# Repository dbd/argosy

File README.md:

# Argosy

Maybe this will be a keyboard one day

### Credits
Footprints from: https://github.com/dnlbauer/corax-keyboard

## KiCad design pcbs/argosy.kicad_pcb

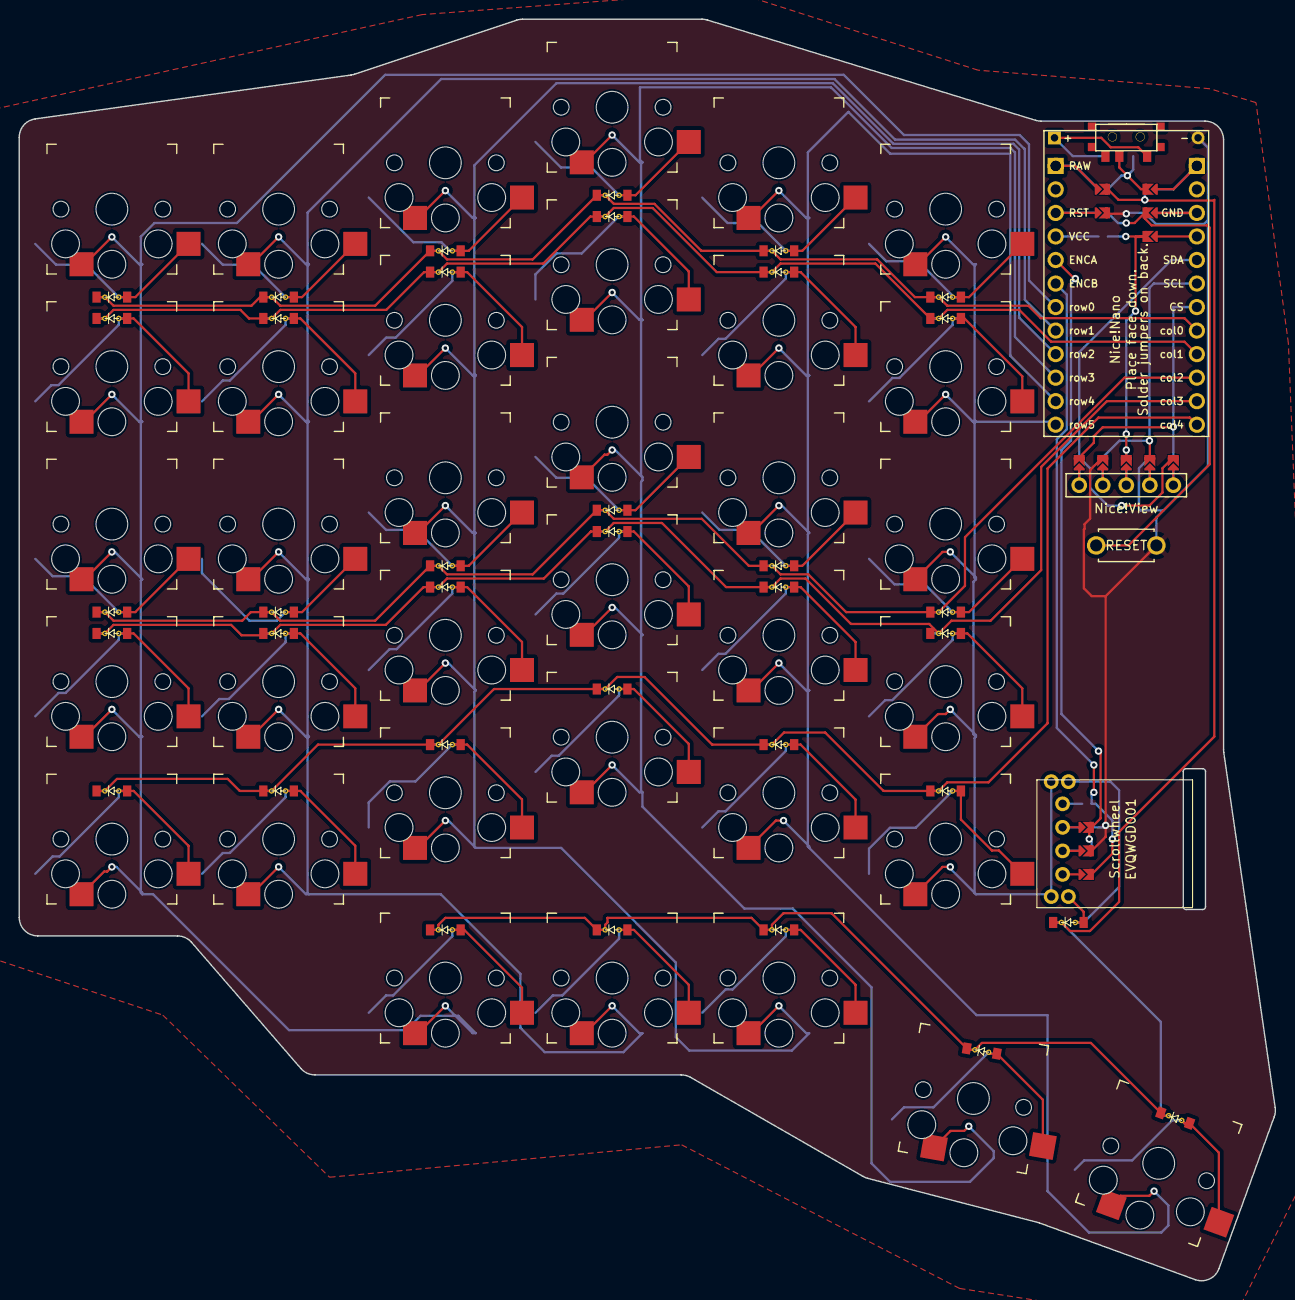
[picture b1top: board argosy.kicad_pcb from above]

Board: 2 copper layers, 135.6 x 136.2 mm, 103 parts (0 on the bottom side), 73 nets.

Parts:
Battery1: niceview_headers
D1, D2, D3, D4, D5, D6, D7, D8, D9, D10, D11, D12, D13, D14, D15, D16, D17, D18, D19, D20, D21, D22, D23, D24, D25, D26, D27, D28, D29, D30, D31, D32, D33, D34, D35, D36: ComboDiode
J1, J2, J3, J4, J5, J6, J7, J8, J9, J10, J11, J12, J13, J14, J15, J16, J17, J18, J19, J20, J21, J22, J23, J24, J25, J26: Jumper
MCU1: ProMicro
Nice!View1: niceview_headers
S1, S2, S3, S4, S5, S6, S7, S8, S9, S10, S11, S12, S13, S14, S15, S16, S17, S18, S19, S20, S21, S22, S23, S24, S25, S26, S27, S28, S29, S30, S31, S32, S33, S34, S35: PG1350
S36: RollerEncoder_Panasonic_EVQWGD001
T1: SPDT_C128955
_1: ResetSW

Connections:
CS: J21.2, J26.2, MCU1.19
ENCA: J3.2, J6.2, MCU1.5
ENCA_GND: J3.1, J5.1, S36.C
ENCB: J1.2, J4.2, MCU1.6
ENCB_undef: J1.1, S36.A
GND: Battery1.2, J2.2, J5.2, J10.2, J15.2, J20.2, J25.2, _1.2
GND_ENCA: J2.1, J6.1, S36.B
GND_RST: J10.1, J13.1, MCU1.15
GND_VCC: J14.1, MCU1.16
NN_CS_SDA: J21.1, J22.1, Nice!View1.1
NN_GND_SCL: J20.1, J23.1, Nice!View1.1
NN_SCL_GND: J18.1, J25.1, Nice!View1.3
NN_SDA_CS: J17.1, J26.1, Nice!View1.4
NN_VCC: J19.1, J24.1, Nice!View1.2
P1: D31.1, D32.1, D33.1, D34.1, D35.1, D36.1, J11.2, J16.2
P1_RAW: J11.1, J12.1, MCU1.13
RAW: J7.2, J12.2, T1.2
RAW_P1: J7.1, J16.1, MCU1.1
RST: J8.2, J13.2, _1.1
RST_GND: J8.1, J15.1, MCU1.3
SCL: J18.2, J23.2, MCU1.18
SDA: J17.2, J22.2, MCU1.17
VCC: J9.2, J14.2, J19.2, J24.2
VCC_GND: J9.1, MCU1.4
alt_cluster: D33.2, S33.2
col0: D2.1, D4.1, D6.1, D8.1, D10.1, D12.1, MCU1.20
col1: D15.1, D18.1, D21.1, D24.1, D27.1, D30.1, MCU1.21
col2: D1.1, D3.1, D5.1, D7.1, D9.1, D11.1, MCU1.22
col3: D14.1, D17.1, D20.1, D23.1, D26.1, D29.1, MCU1.23
col4: D13.1, D16.1, D19.1, D22.1, D25.1, D28.1, MCU1.24
end_cluster: D31.2, S31.2
index_home: D9.2, S23.2
index_lower: D26.2, S22.2
index_mods: D25.2, S21.2
index_number: D10.2, S25.2
index_upper: D27.2, S24.2
inner_home: D11.2, S28.2
inner_lower: D29.2, S27.2
inner_mods: D28.2, S26.2
inner_number: D12.2, S30.2
inner_upper: D30.2, S29.2
layer_cluster: D35.2, S35.2
middle_home: D7.2, S18.2
middle_lower: D23.2, S17.2
middle_mods: D22.2, S16.2
middle_number: D8.2, S20.2
middle_upper: D24.2, S19.2
mute_cluster: D32.2, S32.2
outer_home: D1.2, S3.2
outer_lower: D14.2, S2.2
outer_mods: D13.2, S1.2
outer_number: D2.2, S5.2
outer_upper: D15.2, S4.2
pinky_home: D3.2, S8.2
pinky_lower: D17.2, S7.2
pinky_mods: D16.2, S6.2
pinky_number: D4.2, S10.2
pinky_upper: D18.2, S9.2
ring_home: D5.2, S13.2
ring_lower: D20.2, S12.2
ring_mods: D19.2, S11.2
ring_number: D6.2, S15.2
ring_upper: D21.2, S14.2
row0: MCU1.7, S1.1, S2.1, S3.1, S4.1, S5.1, S31.1
row1: MCU1.8, S6.1, S7.1, S8.1, S9.1, S10.1, S32.1
row2: MCU1.9, S11.1, S12.1, S13.1, S14.1, S15.1, S33.1
row3: MCU1.10, S16.1, S17.1, S18.1, S19.1, S20.1, S34.1
row4: MCU1.11, S21.1, S22.1, S23.1, S24.1, S25.1, S35.1
row5: MCU1.12, S26.1, S27.1, S28.1, S29.1, S30.1, S36.S1
scrollwheel_scrollwheel: D36.2, S36.S2
space_cluster: D34.2, S34.2
switch_from: Battery1.1, T1.1
undef_ENCB: J4.1, S36.D

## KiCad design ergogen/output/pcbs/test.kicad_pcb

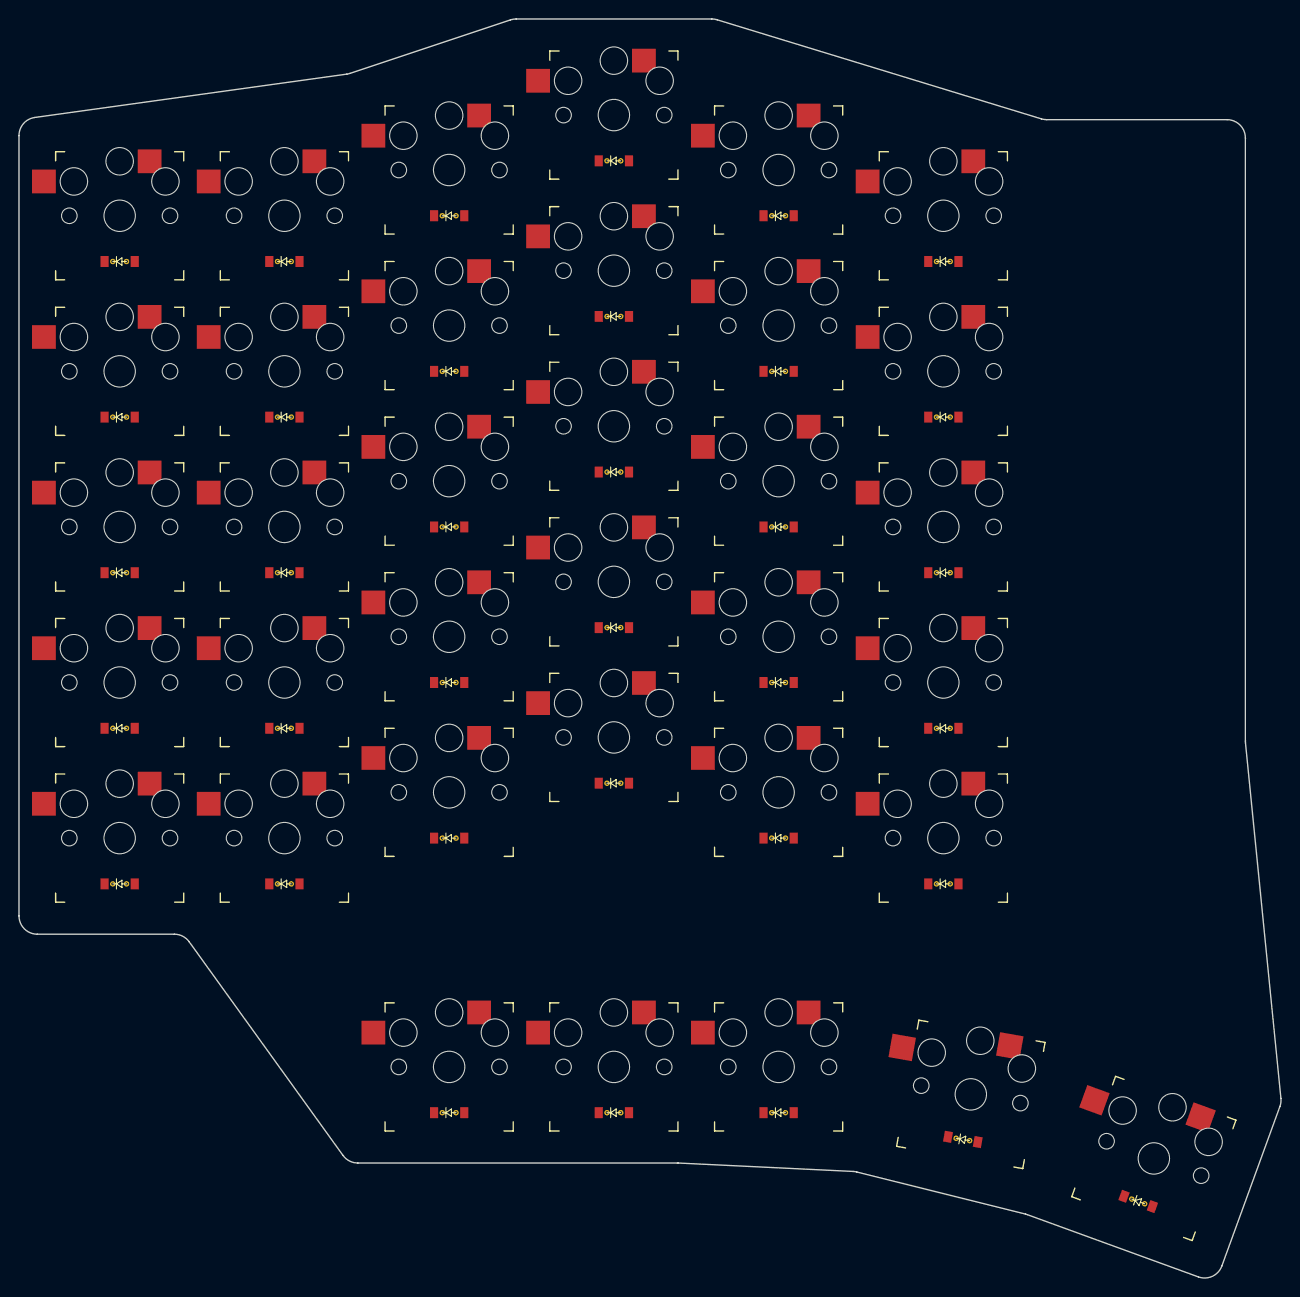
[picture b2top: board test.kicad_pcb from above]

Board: 2 copper layers, 137.9 x 137.6 mm, 70 parts (0 on the bottom side), 47 nets, no tracks yet.

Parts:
D1, D2, D3, D4, D5, D6, D7, D8, D9, D10, D11, D12, D13, D14, D15, D16, D17, D18, D19, D20, D21, D22, D23, D24, D25, D26, D27, D28, D29, D30, D31, D32, D33, D34, D35: ComboDiode
S1, S2, S3, S4, S5, S6, S7, S8, S9, S10, S11, S12, S13, S14, S15, S16, S17, S18, S19, S20, S21, S22, S23, S24, S25, S26, S27, S28, S29, S30, S31, S32, S33, S34, S35: PG1350

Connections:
P6: D31.1, D32.1, D33.1, D34.1, D35.1
P7: D1.1, D6.1, D11.1, D16.1, D21.1, D26.1
P8: D2.1, D7.1, D12.1, D17.1, D22.1, D27.1
P9: D3.1, D8.1, D13.1, D18.1, D23.1, D28.1
P10: D4.1, D9.1, D14.1, D19.1, D24.1, D29.1
P14: S26.2, S27.2, S28.2, S29.2, S30.2, S35.2
P15: S21.2, S22.2, S23.2, S24.2, S25.2, S34.2
P16: D5.1, D10.1, D15.1, D20.1, D25.1, D30.1
P18: S16.2, S17.2, S18.2, S19.2, S20.2, S33.2
P19: S11.2, S12.2, S13.2, S14.2, S15.2, S32.2
P20: S6.2, S7.2, S8.2, S9.2, S10.2, S31.2
P21: S1.2, S2.2, S3.2, S4.2, S5.2
five_five: D25.2, S25.1
five_four: D24.2, S24.1
five_one: D21.2, S21.1
five_three: D23.2, S23.1
five_two: D22.2, S22.1
four_five: D20.2, S20.1
four_four: D19.2, S19.1
four_mods: D35.2, S35.1
four_one: D16.2, S16.1
four_three: D18.2, S18.1
four_two: D17.2, S17.1
one_five: D5.2, S5.1
one_four: D4.2, S4.1
one_mods: D32.2, S32.1
one_one: D1.2, S1.1
one_three: D3.2, S3.1
one_two: D2.2, S2.1
six_five: D30.2, S30.1
six_four: D29.2, S29.1
six_one: D26.2, S26.1
six_three: D28.2, S28.1
six_two: D27.2, S27.1
three_five: D15.2, S15.1
three_four: D14.2, S14.1
three_mods: D34.2, S34.1
three_one: D11.2, S11.1
three_three: D13.2, S13.1
three_two: D12.2, S12.1
two_five: D10.2, S10.1
two_four: D9.2, S9.1
two_mods: D33.2, S33.1
two_one: D6.2, S6.1
two_three: D8.2, S8.1
two_two: D7.2, S7.1
zero_mods: D31.2, S31.1

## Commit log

2024-10-21 [ergogen] rename config rows/columns
2024-10-24 [ergogen] update config and footprints refs
2024-11-11 fix missing pins
2024-11-19 config.yaml
2024-11-19 [pcbs] add single missing trace for thumb cluster key
